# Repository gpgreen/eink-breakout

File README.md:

# Eink-Breakout
Kicad project for a [Dalian Good Display](https://www.good-display.com/) Epaper breakout board. The
display [GDEW042T2](https://www.good-display.com/product/226.html) has
a 24pin flat panel cable. The display is controlled with the SPI bus,
so the display SPI pins are passed to a JST PH connector.

Note: R1 is shown on the datasheet example circuit. It is not needed so should not be
populated on the board.

## Functions
The main function of the board is to translate the signals from the
flat panel cable to the JST PH connector. The JST connector has
signals for the SPI bus, D/C, Busy from the eink display. Also power
and ground at 3.3VDC.

The rest of the conductors on the flat panel cable are connected as
shown in the datasheet example wiring. There is no bus translation,
everything is set at 3.3VDC.

 - [Schematic](eink-breakout-sch-v1.1.pdf)

## PCB

 - 
 - [Parts List](eink-breakout.ods)

## License

Licensed under

- MIT license ([LICENSE-MIT](LICENSE-MIT) or http://opensource.org/licenses/MIT)

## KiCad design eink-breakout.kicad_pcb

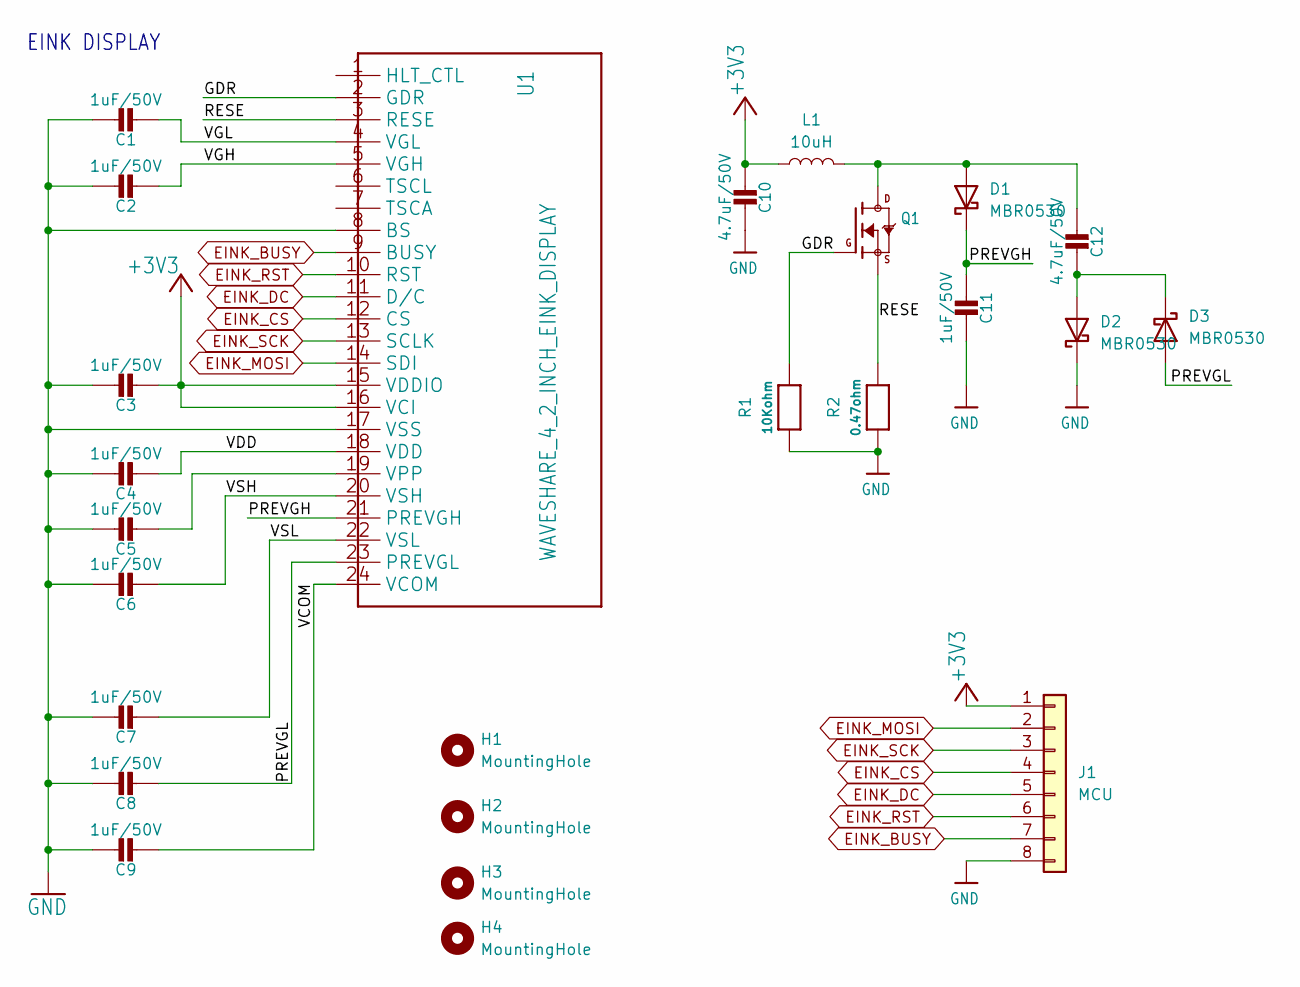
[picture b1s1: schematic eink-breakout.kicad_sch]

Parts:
C1, C2, C3, C4, C5, C6, C7, C8, C9, C11: 1uF/50V; C_0603_1608Metric
C10, C12: 4.7uF/50V; C_1206_3216Metric
D1, D2, D3: MBR0530; D_SOD-123
H1, H2, H3, H4: MountingHole; MountingHole_3.2mm_M3_DIN965
J1: MCU; JST_PH_S8B-PH-SM4-TB_1x08-1MP_P2.00mm_Horizontal
L1: 10uH; IND_IFSC_1515AH_VIS-M
Q1: IRLML0100; SOT-23-3
R1: 10Kohm; R_0603_1608Metric
R2: 0.47ohm; R_0603_1608Metric
U1: WAVESHARE_4_2_INCH_EINK_DISPLAY; AMPHENOL_SFV24R-4STBE1HLF

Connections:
+3V3: C3.2, C10.1, J1.1, L1.1, U1.15 (VDDIO), U1.16 (VCI)
/GDR: Q1.1 (G), R1.1, U1.2 (GDR)
/PREVGH: C11.1, D1.1 (K), U1.21 (PREVGH)
/PREVGL: C8.2, D3.2 (A), U1.23 (PREVGL)
/RESE: Q1.2 (S), R2.1, U1.3 (RESE)
/VCOM: C9.2, U1.24 (VCOM)
/VDD: C4.2, U1.18 (VDD)
/VGH: C2.2, U1.5 (VGH)
/VGL: C1.2, U1.4 (VGL)
/VSH: C6.2, U1.20 (VSH)
/VSL: C7.2, U1.22 (VSL)
EINK_BUSY: J1.7, U1.9 (BUSY)
EINK_CS: J1.4, U1.12 (CS)
EINK_DC: J1.5, U1.11 (D/C)
EINK_MOSI: J1.2, U1.14 (SDI)
EINK_RST: J1.6, U1.10 (RST)
EINK_SCK: J1.3, U1.13 (SCLK)
GND: C1.1, C2.1, C3.1, C4.1, C5.1, C6.1, C7.1, C8.1, C9.1, C10.2, C11.2, D2.1 (K), J1.8, R1.2, R2.2, U1.8 (BS), U1.17 (VSS)
unnamed: C12.1, D1.2 (A), L1.2, Q1.3 (D)
unnamed: C12.2, D2.2 (A), D3.1 (K)
unnamed: C5.2, U1.19 (VPP)

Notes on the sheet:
EINK DISPLAY

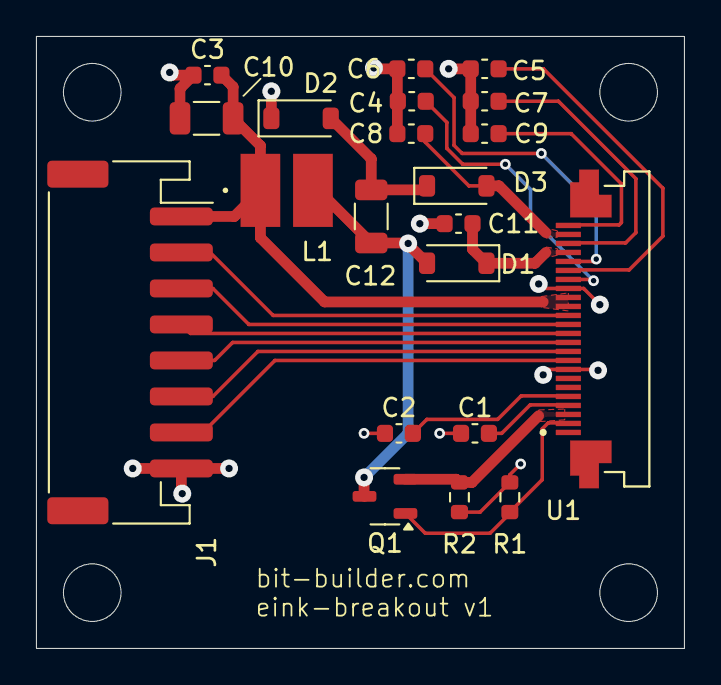
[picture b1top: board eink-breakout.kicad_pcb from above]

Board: 2 copper layers, 36.0 x 34.0 mm, 25 parts (0 on the bottom side), 21 nets.

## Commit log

2025-04-15 Ready for gerbers
2025-04-20 Updated README.md
    Centered symbols in schematic
    Added png of pcb board
    Renamed license file
2025-04-30 DNP of R1
    Datasheet showed R1 attached to gate of mosfet, this was
    incorrect. Fixed in this version by not populating footprint.
2025-04-30 Updated url of schematic
